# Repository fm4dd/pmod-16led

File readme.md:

## 16LED PMOD

### Description

This PMOD provides a sixteen LED display output to FPGA designs via two double-row PMODs.
[fpga.fm4dd.com](http://fpga.fm4dd.com)

### Schematic

### Pin Assignments

#### IceBreaker v1.0

 J1# |  Label | Description   | PMOD1A
-----|--------|---------------|-------
1    |  D1    | LED D1        | 4
7    |  D2    | LED D2        | 3
2    |  D3    | LED D3        | 2
8    |  D4    | LED D4        | 48
3    |  D5    | LED D5        | 47
9    |  D6    | LED D6        | 46
4    |  D7    | LED D7        | 45
10   |  D8    | LED D8        | 44

 J2# |  Label | Description   | PMOD1B
-----|--------|---------------|-------
1    |  D9    | LED D9        | 43
7    |  D10   | LED D10       | 42
2    |  D11   | LED D11       | 38
8    |  D12   | LED D12       | 36
3    |  D13   | LED D13       | 44
9    |  D14   | LED D14       | 32
4    |  D15   | LED D15       | 31
10   |  D16   | LED D16       | 28

#### DE0-Nano-SoC

 J1# |  Label | Description   | GPIO0A | GPIO1A
-----|--------|---------------|--------|--------
1    |  D2    | LED D1        | PIN_AF8|PIN_AH27
2    |  D1    | LED D2        | PIN_W12|PIN_AA15
3    |  D4    | LED D3        | PIN_AB4|PIN_AH24
4    |  D3    | LED D4        | PIN_Y8 |PIN_AG26
7    |  D6    | LED D5        | PIN_Y4 |PIN_AE22
8    |  D5    | LED D6        | PIN_W8 |PIN_AF23
9    |  D8    | LED D7        | PIN_U11|PIN_AG20
10   |  D7    | LED D8        | PIN_Y5 |PIN_AF21

 J2# |  Label | Description   | GPIO0B | GPIO1B
-----|--------|---------------|--------|--------
1    |  D13   | LED D13       | PIN_AG6| PIN_AD19
2    |  D9    | LED D9        | PIN_AF4| PIN_AH23
3    |  D14   | LED D14       | PIN_AE4| PIN_AE20
4    |  D10   | LED D10       | PIN_AF5| PIN_AG23
7    |  D15   | LED D15       | PIN_T11| PIN_AE24
8    |  D11   | LED D11       | PIN_T13| PIN_AE19
9    |  D16   | LED D16       | PIN_AF6| PIN_AD20
10   |  D12   | LED D12       | PIN_AE7| PIN_AF18

### Example Code

#### Verilog

Verilog test program pmod16led_1.v (top-level):
```
// -------------------------------------------------------
// This program is a binary counter displayed on the
// on the pmod D2-8, and 9-16. D1 is pulsing 1Hz clock.
// 12MHz clock: set breakpoint at 23'd5999999
// 50MHz clock: set breakpoint at 25'd24999999
// -------------------------------------------------------
module pmod16led_1 (
  input clk,
  output reg [0:7] pmodled1,
  output reg [0:7] pmodled2,
);

  reg [22:0] count = 23'd0;
  reg clk_1hz = 1'b0;
  assign pmodled1[0] = clk_1hz;

  reg [6:0] lednum1 = 7'd0;
  assign pmodled1[7:1] = lednum1;

  reg [7:0] lednum2 = 8'd0;
  assign pmodled2[7:0] = lednum2;

  always @(posedge clk)
  begin
    count   <= count + 1;
    if(count == 23'd5999999)
    begin
      count   <= 0;
      clk_1hz <= ~clk_1hz;
      lednum1 <= lednum1 + 1;
      lednum2 <= lednum2 + 1;
    end
  end
endmodule
```
#### VHDL

This is Verilog test program pmod16led_1.v converted to VHDL as pmod16led_2.vhd

```
library ieee;
use ieee.std_logic_1164.all;
use ieee.numeric_std.all;

entity pmod_16led_2 is
port (
       clk: in STD_LOGIC;
  pmodled1: out STD_LOGIC_VECTOR(0 to 7) := "00000000";
  pmodled2: out STD_LOGIC_VECTOR(0 to 7) := "00000000"
);
end pmod_16led_2;

architecture arch of pmod_16led_2 is
  signal clk_1hz: STD_LOGIC := '0';
  signal  lednum1: STD_LOGIC_VECTOR(6 downto 0) := "0000000";
  signal  lednum2: STD_LOGIC_VECTOR(7 downto 0) := "00000000";

  begin
    counter_p: process( clk, clk_1hz, lednum1, lednum2 )
    variable count: INTEGER := 0;
    begin
      if( rising_edge(clk) ) then
        count := count + 1;
        if( count = 24999999 ) then
          count := 0;
          clk_1hz <= NOT clk_1hz;
          lednum1 <= std_logic_vector( unsigned(lednum1) + 1);
          lednum2 <= std_logic_vector( unsigned(lednum2) + 1);
        end if;
      end if;

    pmodled1(0) <= clk_1hz;
    pmodled1(1) <= lednum1(6);
    pmodled1(2) <= lednum1(5);
    pmodled1(3) <= lednum1(4);
    pmodled1(4) <= lednum1(3);
    pmodled1(5) <= lednum1(2);
    pmodled1(6) <= lednum1(1);
    pmodled1(7) <= lednum1(0);

    pmodled2 <= lednum2;
  end process counter_p;
end arch;
```

16LED Pmod on a iceBreaker board

16LED Pmod on a 85K ULX3S board

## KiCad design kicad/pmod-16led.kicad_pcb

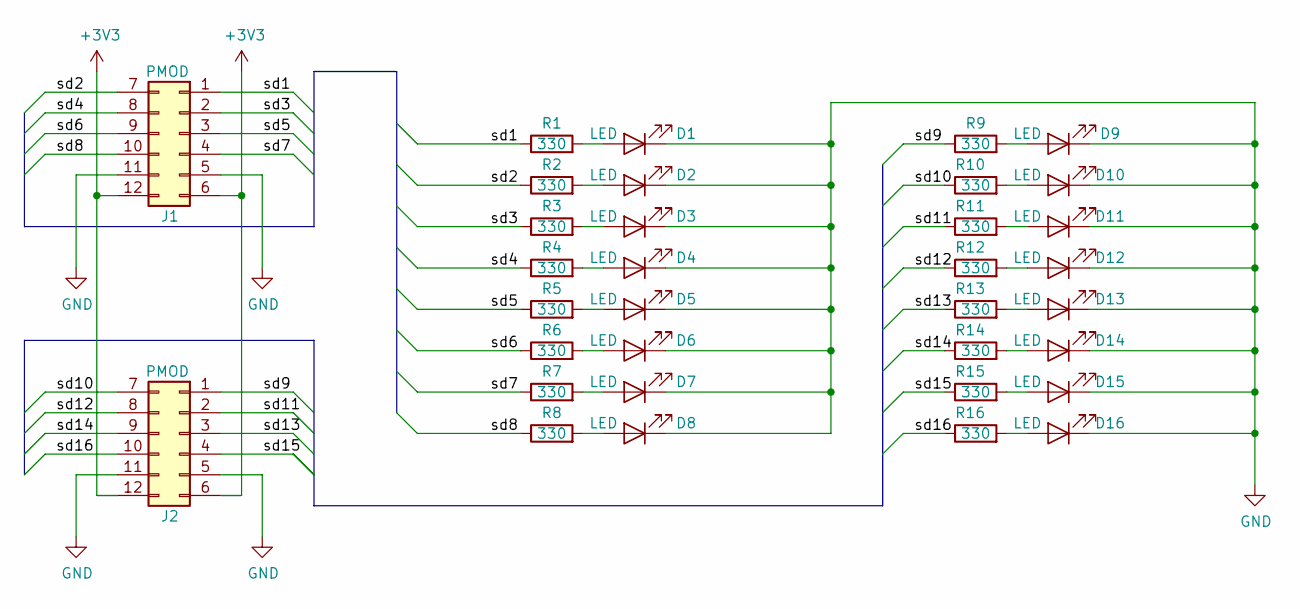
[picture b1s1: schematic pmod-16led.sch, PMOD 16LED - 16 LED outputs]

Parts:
D1, D2, D3, D4, D5, D6, D7, D8, D9, D10, D11, D12, D13, D14, D15, D16: LED; LED_3020Metric_Pad1.42x2.65mm_HandSolder
J1, J2: PMOD; PMODHeader_2x06_P2.54mm_Horizontal
R1, R2, R3, R4, R5, R6, R7, R8, R9, R10, R11, R12, R13, R14, R15, R16: 330; R_2010_5025Metric

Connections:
+3V3: J1.6, J1.12, J2.6, J2.12
/sd1: J1.1, R1.1
/sd2: J1.7, R2.1
/sd3: J1.2, R3.1
/sd4: J1.8, R4.1
/sd5: J1.3, R5.1
/sd6: J1.9, R6.1
/sd7: J1.4, R7.1
/sd8: J1.10, R8.1
/sd9: J2.1, R9.1
/sd10: J2.7, R10.1
/sd11: J2.2, R11.1
/sd12: J2.8, R12.1
/sd13: J2.3, R13.1
/sd14: J2.9, R14.1
/sd15: J2.4, R15.1
/sd16: J2.10, R16.1
GND: D1.1 (K), D2.1 (K), D3.1 (K), D4.1 (K), D5.1 (K), D6.1 (K), D7.1 (K), D8.1 (K), D9.1 (K), D10.1 (K), D11.1 (K), D12.1 (K), D13.1 (K), D14.1 (K), D15.1 (K), D16.1 (K), J1.5, J1.11, J2.5, J2.11
unnamed: D1.2 (A), R1.2
unnamed: D2.2 (A), R2.2
unnamed: D3.2 (A), R3.2
unnamed: D4.2 (A), R4.2
unnamed: D5.2 (A), R5.2
unnamed: D6.2 (A), R6.2
unnamed: D7.2 (A), R7.2
unnamed: D8.2 (A), R8.2
unnamed: D9.2 (A), R9.2
unnamed: D10.2 (A), R10.2
unnamed: D11.2 (A), R11.2
unnamed: D12.2 (A), R12.2
unnamed: D13.2 (A), R13.2
unnamed: D14.2 (A), R14.2
unnamed: D15.2 (A), R15.2
unnamed: D16.2 (A), R16.2

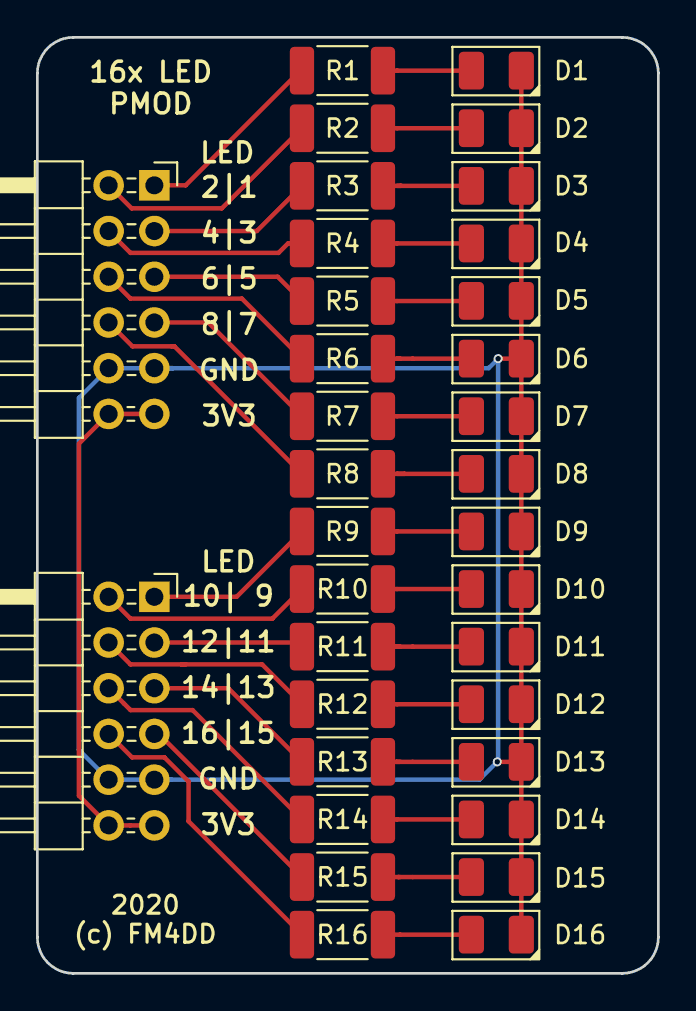
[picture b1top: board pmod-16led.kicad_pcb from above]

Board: 2 copper layers, 34.5 x 52.0 mm, 34 parts (0 on the bottom side), 34 nets.

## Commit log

2020-03-20 verilog and pin # update
2020-03-20 add fpga url
2020-04-02 fix pin assignment and add VHDL example
2020-04-04 update schema, add BOM
2020-04-04 mend
2020-04-19 add Verilog/VHDL demo code
2020-04-23 fix git lang discovery
2020-11-17 add ULX3S example
2020-12-02 add VHDL examples

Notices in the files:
kicad/pmod-16led.kicad_pcb:
License: CC-BY-SA 4.0
CC-BY-SA
